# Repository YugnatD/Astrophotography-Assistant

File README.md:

# Astrophotography-Assistant

The project has two utility :
Make an automatic regulation of the temperature of the mirror of a newtonian telescope.
Recreate a card to controle motor of a NEQ5 mount, to add more correction speed, and planetary speed.

There is a raspberry pi integrated to the card that can control a guiding camera using PHD2.

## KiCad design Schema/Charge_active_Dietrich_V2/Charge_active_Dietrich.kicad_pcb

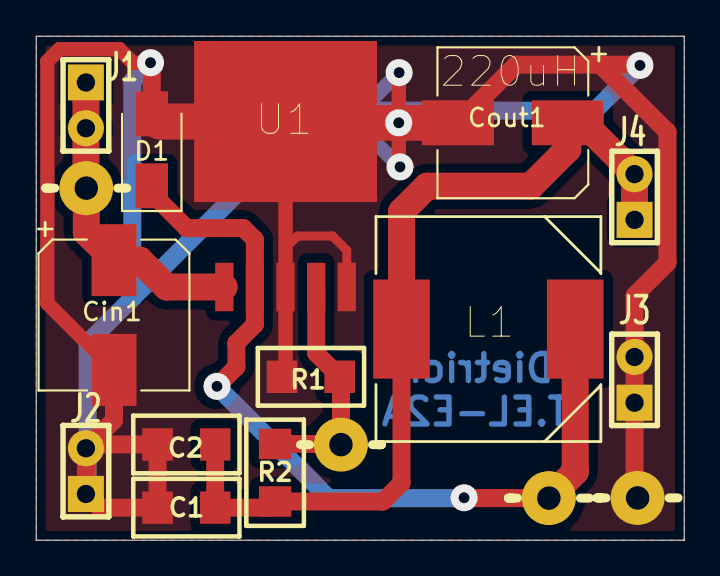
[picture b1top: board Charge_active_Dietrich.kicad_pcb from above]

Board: 2 copper layers, 36.0 x 28.0 mm, 17 parts (0 on the bottom side), 5 nets.

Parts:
C1, C2: C; SM_C_1206
Cin1: 100uF; CP_Elec_8x10
Cout1: 100uF; CP_Elec_8x10
D1: MBR340; D_SMA
J1, J2, J3, J4: CON2; TSC_CON2_SIL
J5, J6, J7, J8: CON1; TSC_CON1_poignard
L1: 220uH; INDM125125X800N
R1: 1K; SM_R_1206
R2: 3K; SM_R_1206
U1: LM2575HVS-ADJ; TO170P1435X457-6N

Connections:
GND: C1.2, C2.2, Cin1.2, Cout1.2, D1.2, J2.1, J2.2, J3.1, J3.2, J5.1, R1.2, U1.3, U1.5, U1.6
unnamed: C1.1, C2.1, Cout1.1, J4.1, J4.2, L1.2, R2.1
unnamed: Cin1.1, J1.1, J1.2, J8.1, U1.1
unnamed: D1.1, J6.1, L1.1, U1.2
unnamed: J7.1, R1.1, R2.2, U1.4

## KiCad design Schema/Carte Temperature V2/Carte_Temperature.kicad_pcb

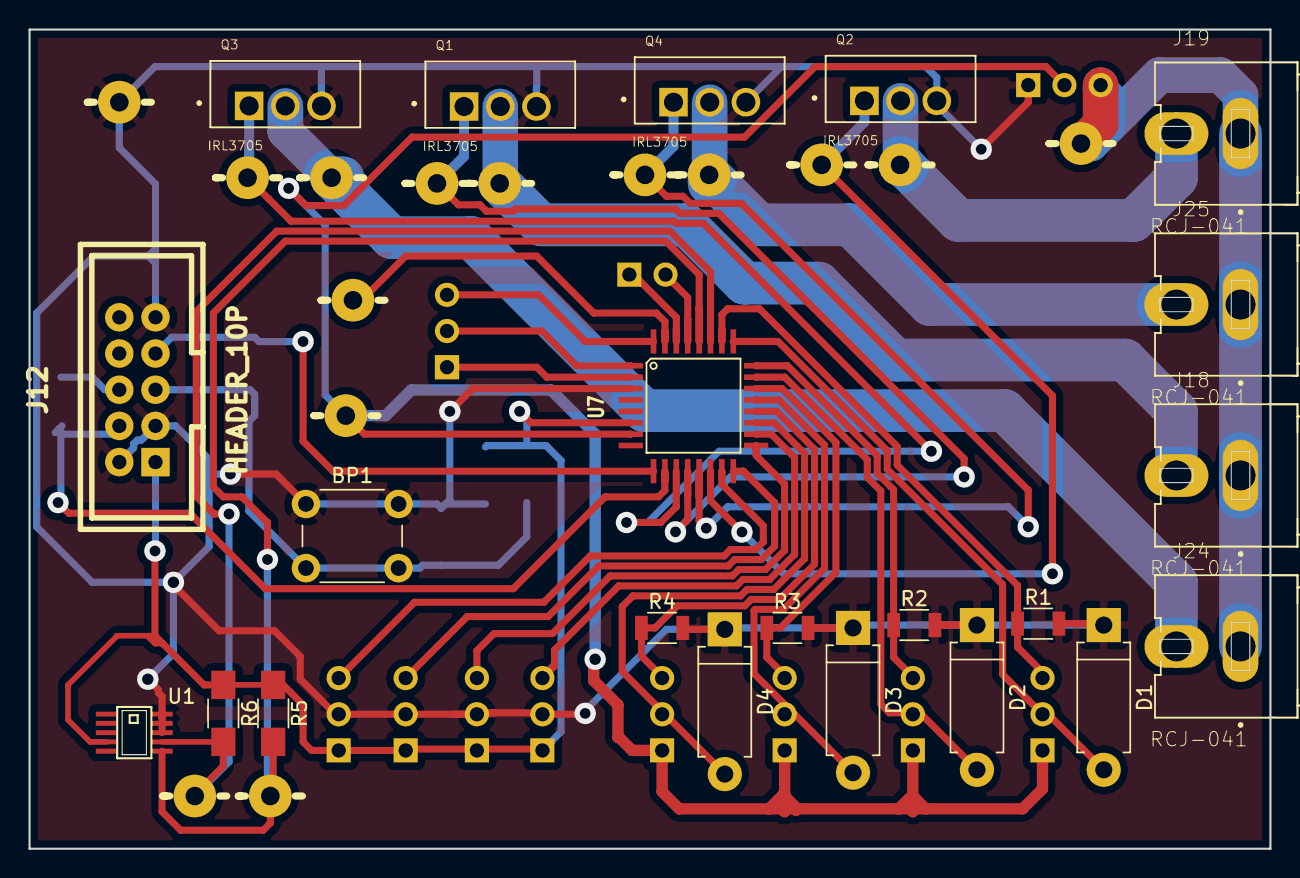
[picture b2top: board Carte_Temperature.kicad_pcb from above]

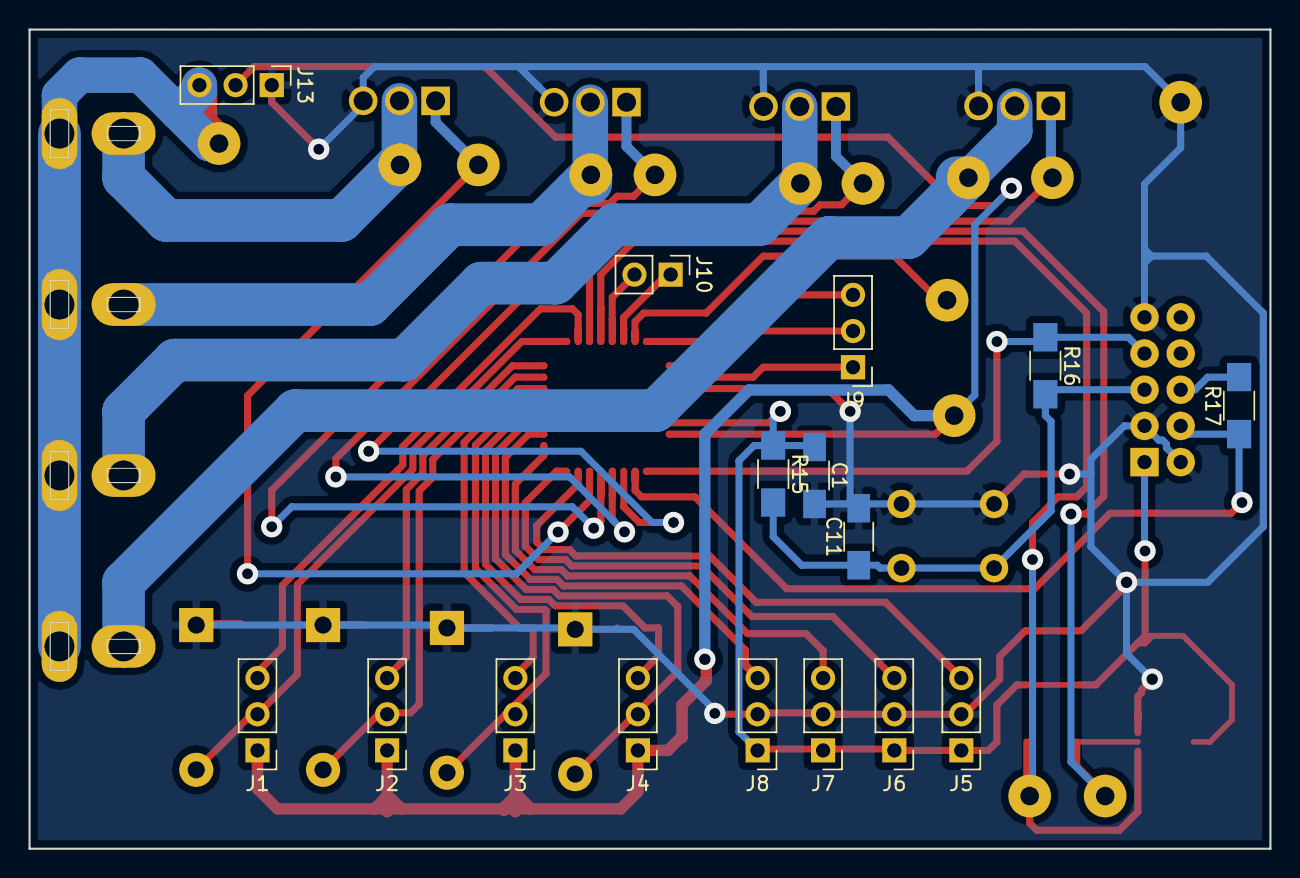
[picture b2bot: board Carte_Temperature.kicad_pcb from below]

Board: 2 copper layers, 87.1 x 57.5 mm, 52 parts (16 on the bottom side), 36 nets.

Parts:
BP1: POUSSOIR_ON; SW_PUSH_6mm
C1: C; C_1206_HandSoldering
C11: 1uF; C_1206_HandSoldering
D1, D2, D3, D4: D; D_DO-15_P10.16mm_Horizontal
J1, J2, J3, J4, J5, J6, J7, J8, J9, J13: Conn_01x03; Pin_Header_Straight_1x03_Pitch2.54mm
J10: Conn_01x02; Pin_Header_Straight_1x02_Pitch2.54mm
J11, J14, J15, J16, J17, J20, J21, J22, J23, J26, J27, J28, J29, J30: Conn_01x01; TSC_CON1_poignard
J12: HEADER_10P; JTAG
J18, J19, J24, J25: RCJ-041; CUI_RCJ-041_Graveuse
Q1, Q2, Q3, Q4: IRL3705; TO254P1052X465X1989-3-IRL3705
R1, R2, R3, R4: 18k; R_1206
R5, R6: R; R_1206_HandSoldering
R15, R16, R17: 1K; R_1206_HandSoldering
U1: EEH210; EEH210_1.5mm
U7: C8051F38C

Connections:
/C8051F38C/P0.0: J9.1, U7.2
/C8051F38C/P0.1: J9.2, U7.1
/C8051F38C/P0.2: J9.3, U7.32
/C8051F38C/P0.3: J11.1, U7.31
/C8051F38C/P0.4: J10.1, U7.30
/C8051F38C/P0.5: J10.2, U7.29
/C8051F38C/P0.6: J26.1, R5.2, U1.6, U7.28
/C8051F38C/P0.7: J27.1, R6.2, U1.7, U7.27
GND: BP1.1, C1.2, C11.2, D1.1, D2.1, D3.1, D4.1, J5.2, J6.2, J7.2, J8.2, J12.2, J12.3, J12.9, J13.1, J30.1, Q1.3, Q2.3, Q3.3, Q4.3, R1.2, R2.2, R3.2, R4.2, U1.8, U1.9, U1.10, U7.3
LM35_0_NEG: D1.2, J1.2, U7.25
LM35_0_POS: J1.3, R1.1, U7.26
LM35_1_NEG: D2.2, J2.2, U7.23
LM35_1_POS: J2.3, R2.1, U7.24
LM35_2_NEG: D3.2, J3.2, U7.21
LM35_2_POS: J3.3, R3.1, U7.22
LM35_3_NEG: D4.2, J4.2, U7.19
LM35_3_POS: J4.3, R4.1, U7.20
unnamed: BP1.2, C11.1, J12.5, R15.2, R16.2
unnamed: J12.4, R17.1, U7.10
unnamed: J12.6, R17.2
unnamed: J12.7, R16.1, U7.9
unnamed: J16.1, J18.2, Q1.2
unnamed: J17.1, J19.2, Q2.2
unnamed: J22.1, J24.2, Q3.2
unnamed: J23.1, J25.2, Q4.2
PCA0: J15.1, Q2.1, U7.14
PCA1: J21.1, Q4.1, U7.13
PCA2: J14.1, Q1.1, U7.12
PCA3: J20.1, Q3.1, U7.11
POT_0: J8.3, U7.18
POT_1: J7.3, U7.17
POT_2: J6.3, U7.16
POT_3: J5.3, U7.15
V(12V): J13.3, J18.1, J19.1, J24.1, J25.1, J29.1
VCC(5V): J1.1, J2.1, J3.1, J4.1, J13.2, J28.1, U7.7
VDD(3.3V): C1.1, J5.1, J6.1, J7.1, J8.1, J12.1, R5.1, R6.1, R15.1, U1.4, U7.6

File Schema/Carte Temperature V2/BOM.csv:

Source:;C:/Users/DIETRICHT_ELEC/Desktop/Diplome_Telescope_Dietrich_V17/Kicad_Telescope_V6/Carte Temperature V2/Carte_Temperature.sch;;;;;
Date:;24.05.2019 10:35;;;;;
Tool:;Eeschema 4.0.7;;;;;
Generator:;C:/Program Files/KiCad/bin/scripting/plugins/bom_csv_grouped_by_value.py;;;;;
Component Count:;52;;;;;
;;;;;;
Individual Components:;;;;;;
;;;;;;
Item;Qty;Reference(s);Value;LibPart;Footprint;Datasheet
;;BP1;POUSSOIR_ON;Carte_Temperature-cache:POUSSOIR_ON;Buttons_Switches_THT:SW_PUSH_6mm;
;;C1;100nF;device:C;Capacitors_SMD:C_1206_HandSoldering;
;;C11;1uF;device:C;Capacitors_SMD:C_1206_HandSoldering;
;;D1;D;device:D;Diodes_THT:D_DO-15_P10.16mm_Horizontal;
;;D2;D;device:D;Diodes_THT:D_DO-15_P10.16mm_Horizontal;
;;D3;D;device:D;Diodes_THT:D_DO-15_P10.16mm_Horizontal;
;;D4;D;device:D;Diodes_THT:D_DO-15_P10.16mm_Horizontal;
;;J1;Conn_01x03;conn:Conn_01x03;Pin_Headers:Pin_Header_Straight_1x03_Pitch2.54mm;
;;J2;Conn_01x03;conn:Conn_01x03;Pin_Headers:Pin_Header_Straight_1x03_Pitch2.54mm;
;;J3;Conn_01x03;conn:Conn_01x03;Pin_Headers:Pin_Header_Straight_1x03_Pitch2.54mm;
;;J4;Conn_01x03;conn:Conn_01x03;Pin_Headers:Pin_Header_Straight_1x03_Pitch2.54mm;
;;J5;Conn_01x03;conn:Conn_01x03;Pin_Headers:Pin_Header_Straight_1x03_Pitch2.54mm;
;;J6;Conn_01x03;conn:Conn_01x03;Pin_Headers:Pin_Header_Straight_1x03_Pitch2.54mm;
;;J7;Conn_01x03;conn:Conn_01x03;Pin_Headers:Pin_Header_Straight_1x03_Pitch2.54mm;
;;J8;Conn_01x03;conn:Conn_01x03;Pin_Headers:Pin_Header_Straight_1x03_Pitch2.54mm;
;;J9;Conn_01x03;conn:Conn_01x03;Pin_Headers:Pin_Header_Straight_1x03_Pitch2.54mm;
;;J10;Conn_01x02;conn:Conn_01x02;Pin_Headers:Pin_Header_Straight_1x02_Pitch2.54mm;
;;J11;Conn_01x01;conn:Conn_01x01;base_V2:TSC_CON1_poignard;
;;J12;HEADER_10P;Carte_Temperature-cache:HEADER_10P;Carte_Temperature:JTAG;
;;J13;Conn_01x03;conn:Conn_01x03;Pin_Headers:Pin_Header_Straight_1x03_Pitch2.54mm;
;;J14;Conn_01x01;conn:Conn_01x01;base_V2:TSC_CON1_poignard;
;;J15;Conn_01x01;conn:Conn_01x01;base_V2:TSC_CON1_poignard;
;;J16;Conn_01x01;conn:Conn_01x01;base_V2:TSC_CON1_poignard;
;;J17;Conn_01x01;conn:Conn_01x01;base_V2:TSC_CON1_poignard;
;;J18;RCJ-041;Carte_Temperature:RCJ-041;Carte_Temperature:CUI_RCJ-041_Graveuse;RCJ-041
;;J19;RCJ-041;Carte_Temperature:RCJ-041;Carte_Temperature:CUI_RCJ-041_Graveuse;RCJ-041
;;J20;Conn_01x01;conn:Conn_01x01;base_V2:TSC_CON1_poignard;
;;J21;Conn_01x01;conn:Conn_01x01;base_V2:TSC_CON1_poignard;
;;J22;Conn_01x01;conn:Conn_01x01;base_V2:TSC_CON1_poignard;
;;J23;Conn_01x01;conn:Conn_01x01;base_V2:TSC_CON1_poignard;
;;J24;RCJ-041;Carte_Temperature:RCJ-041;Carte_Temperature:CUI_RCJ-041_Graveuse;RCJ-041
;;J25;RCJ-041;Carte_Temperature:RCJ-041;Carte_Temperature:CUI_RCJ-041_Graveuse;RCJ-041
;;J26;Conn_01x01;conn:Conn_01x01;base_V2:TSC_CON1_poignard;
;;J27;Conn_01x01;conn:Conn_01x01;base_V2:TSC_CON1_poignard;
;;J28;Conn_01x01;conn:Conn_01x01;base_V2:TSC_CON1_poignard;
;;J29;Conn_01x01;conn:Conn_01x01;base_V2:TSC_CON1_poignard;
;;J30;Conn_01x01;conn:Conn_01x01;base_V2:TSC_CON1_poignard;
;;Q1;IRL3705;Carte_Temperature:IRL3705;Carte_Temperature:TO254P1052X465X1989-3-IRL3705;
;;Q2;IRL3705;Carte_Temperature:IRL3705;Carte_Temperature:TO254P1052X465X1989-3-IRL3705;
;;Q3;IRL3705;Carte_Temperature:IRL3705;Carte_Temperature:TO254P1052X465X1989-3-IRL3705;
;;Q4;IRL3705;Carte_Temperature:IRL3705;Carte_Temperature:TO254P1052X465X1989-3-IRL3705;
;;R1;18k;device:R;Resistors_SMD:R_1206_HandSoldering;
;;R2;18k;device:R;Resistors_SMD:R_1206_HandSoldering;
;;R3;18k;device:R;Resistors_SMD:R_1206_HandSoldering;
;;R4;18k;device:R;Resistors_SMD:R_1206_HandSoldering;
;;R5;1k;device:R;Resistors_SMD:R_1206_HandSoldering;
;;R6;1k;device:R;Resistors_SMD:R_1206_HandSoldering;
;;R15;1K;device:R;Resistors_SMD:R_1206_HandSoldering;
;;R16;1K;device:R;Resistors_SMD:R_1206_HandSoldering;
;;R17;1K;device:R;Resistors_SMD:R_1206_HandSoldering;
;;U1;EEH210;Carte_Temperature:EEH210;Carte_Temperature:EEH210_1.5mm;
;;U7;C8051F38C;Carte_Temperature-cache:C8051F38C;Carte_Temperature:C8051F38C;
;;;;;;
;;;;;;
;;;;;;
Collated Components:;;;;;;
;;;;;;
Item;Qty;Reference(s);Value;LibPart;Footprint;Datasheet
1;1;BP1;POUSSOIR_ON;Carte_Temperature-cache:POUSSOIR_ON;Buttons_Switches_THT:SW_PUSH_6mm;
2;1;C1;100nF;device:C;Capacitors_SMD:C_1206_HandSoldering;
3;1;C11;1uF;device:C;Capacitors_SMD:C_1206_HandSoldering;
4;4;"D1; D2; D3; D4";D;device:D;Diodes_THT:D_DO-15_P10.16mm_Horizontal;
5;10;"J1; J2; J3; J4; J5; J6; J7; J8; J9; J13";Conn_01x03;conn:Conn_01x03;Pin_Headers:Pin_Header_Straight_1x03_Pitch2.54mm;
6;1;J10;Conn_01x02;conn:Conn_01x02;Pin_Headers:Pin_Header_Straight_1x02_Pitch2.54mm;
7;14;"J11; J14; J15; J16; J17; J20; J21; J22; J23; J26; J27; J28; J29; J30";Conn_01x01;conn:Conn_01x01;base_V2:TSC_CON1_poignard;
8;1;J12;HEADER_10P;Carte_Temperature-cache:HEADER_10P;Carte_Temperature:JTAG;
9;4;"J18; J19; J24; J25";RCJ-041;Carte_Temperature:RCJ-041;Carte_Temperature:CUI_RCJ-041_Graveuse;RCJ-041
10;4;"Q1; Q2; Q3; Q4";IRL3705;Carte_Temperature:IRL3705;Carte_Temperature:TO254P1052X465X1989-3-IRL3705;
11;4;"R1; R2; R3; R4";18k;device:R;Resistors_SMD:R_1206_HandSoldering;
12;2;"R5; R6";1k;device:R;Resistors_SMD:R_1206_HandSoldering;
13;3;"R15; R16; R17";1K;device:R;Resistors_SMD:R_1206_HandSoldering;
14;1;U1;EEH210;Carte_Temperature:EEH210;Carte_Temperature:EEH210_1.5mm;
15;1;U7;C8051F38C;Carte_Temperature-cache:C8051F38C;Carte_Temperature:C8051F38C;

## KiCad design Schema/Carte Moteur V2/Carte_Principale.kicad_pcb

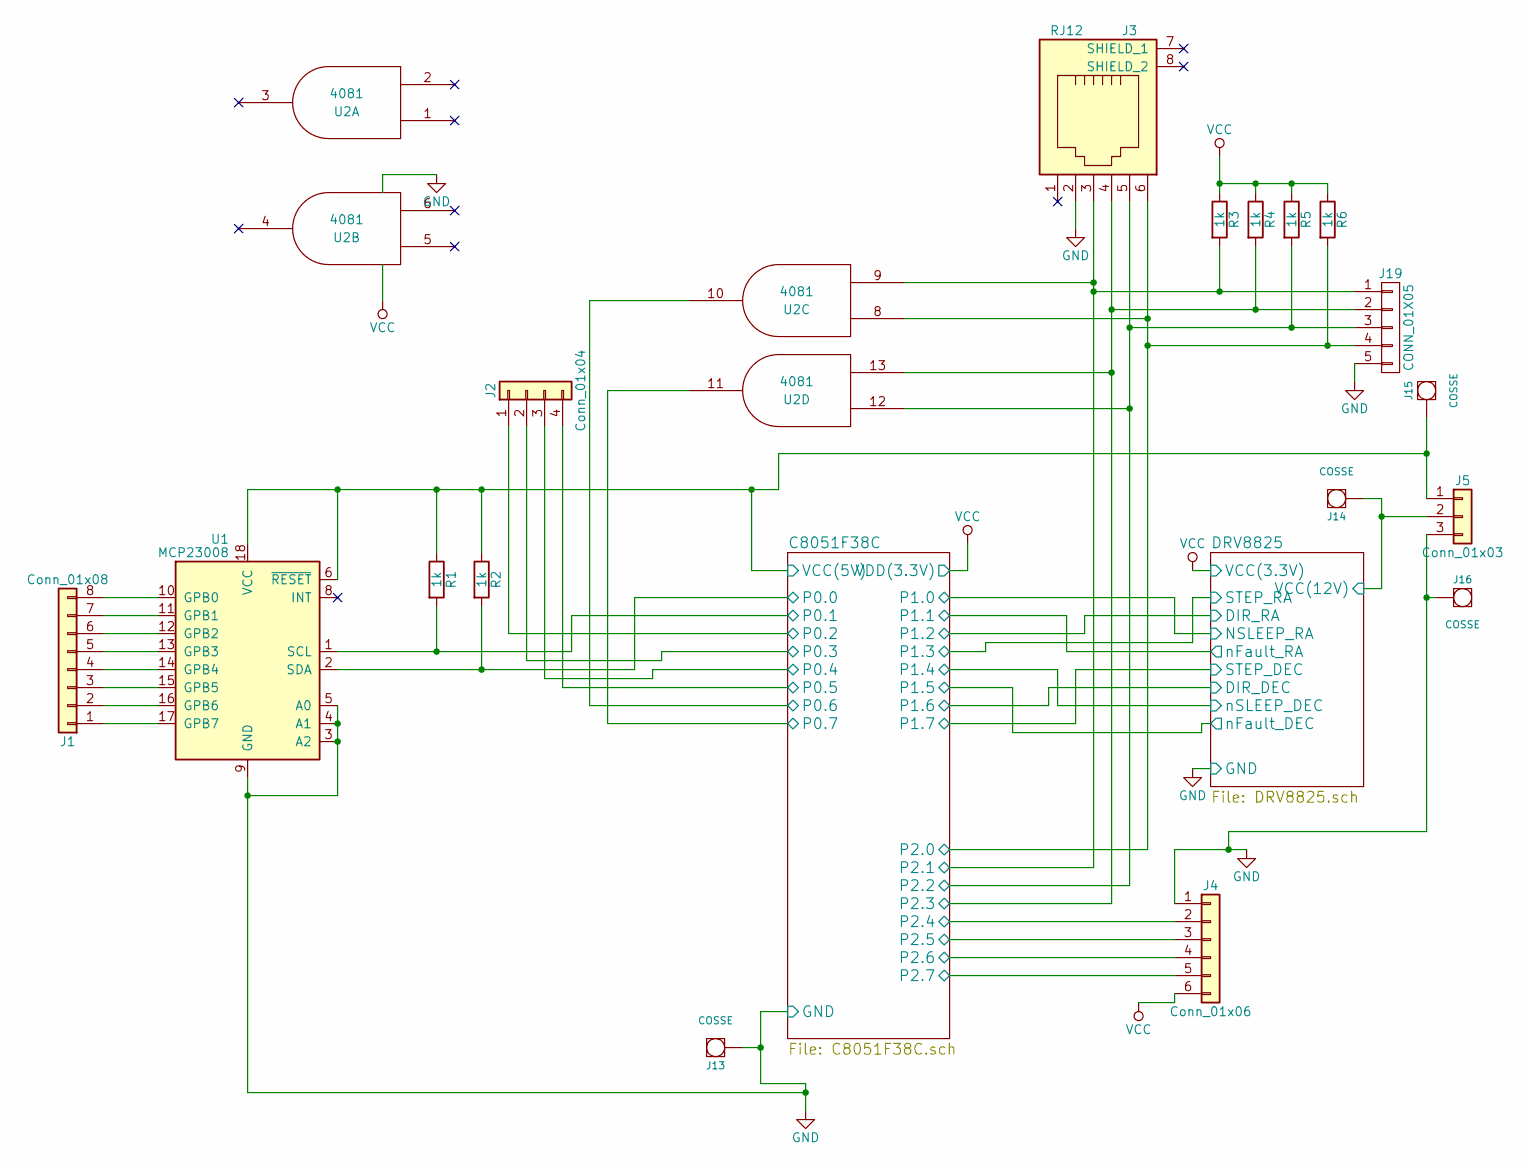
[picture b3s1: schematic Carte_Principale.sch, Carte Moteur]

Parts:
J1: Conn_01x08; Pin_Header_Straight_1x08
J2: Conn_01x04; Pin_Header_Straight_1x04
J3: RJ12
J4: Conn_01x06; Pin_Header_Straight_1x06
J5: Conn_01x03; Pin_Header_Straight_1x03
J13, J14, J15, J16: COSSE; TSC_CON1_poignard
J19: CONN_01X05; Pin_Header_Straight_1x05_Pitch2.54mm
R1, R2, R3, R4, R5, R6: 1k; R_1206_HandSoldering
U1: MCP23008; SOIC-18
U2: 4081; SM_SO-14

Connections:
/C8051F38C/P0.0: R2.2, U1.2 (SDA); also elsewhere on the board
/C8051F38C/P0.1: R1.2, U1.1 (SCL); also elsewhere on the board
/C8051F38C/P0.2: J2.1; also elsewhere on the board
/C8051F38C/P0.3: J2.2; also elsewhere on the board
/C8051F38C/P0.4: J2.3; also elsewhere on the board
/C8051F38C/P0.5: J2.4; also elsewhere on the board
/C8051F38C/P0.6: U2.10; also elsewhere on the board
/C8051F38C/P0.7: U2.11; also elsewhere on the board
/C8051F38C/P2.0: J3.6, J19.4, R6.2, U2.8; also elsewhere on the board
/C8051F38C/P2.1: J3.3, J19.1, R3.2, U2.9; also elsewhere on the board
/C8051F38C/P2.2: J3.5, J19.3, R5.2, U2.12; also elsewhere on the board
/C8051F38C/P2.3: J3.4, J19.2, R4.2, U2.13; also elsewhere on the board
/C8051F38C/P2.4: J4.2; also elsewhere on the board
/C8051F38C/P2.5: J4.3; also elsewhere on the board
/C8051F38C/P2.6: J4.4; also elsewhere on the board
/C8051F38C/P2.7: J4.5; also elsewhere on the board
/C8051F38C/VCC(5V): J5.1, J15.1, R1.1, R2.1, U1.6 (~RESET), U1.18 (VCC); also elsewhere on the board
/DRV8825/VCC(12V): J5.2, J14.1; also elsewhere on the board
GND: J3.2, J4.1, J5.3, J13.1, J16.1, J19.5, U1.3 (A2), U1.4 (A1), U1.5 (A0), U1.9 (GND), U2.7 (VSS); also elsewhere on the board
unnamed: J1.1, U1.17 (GPB7)
unnamed: J1.2, U1.16 (GPB6)
unnamed: J1.3, U1.15 (GPB5)
unnamed: J1.4, U1.14 (GPB4)
unnamed: J1.5, U1.13 (GPB3)
unnamed: J1.6, U1.12 (GPB2)
unnamed: J1.7, U1.11 (GPB1)
unnamed: J1.8, U1.10 (GPB0)
VCC: J4.6, R3.1, R4.1, R5.1, R6.1, U2.14 (VDD); also elsewhere on the board

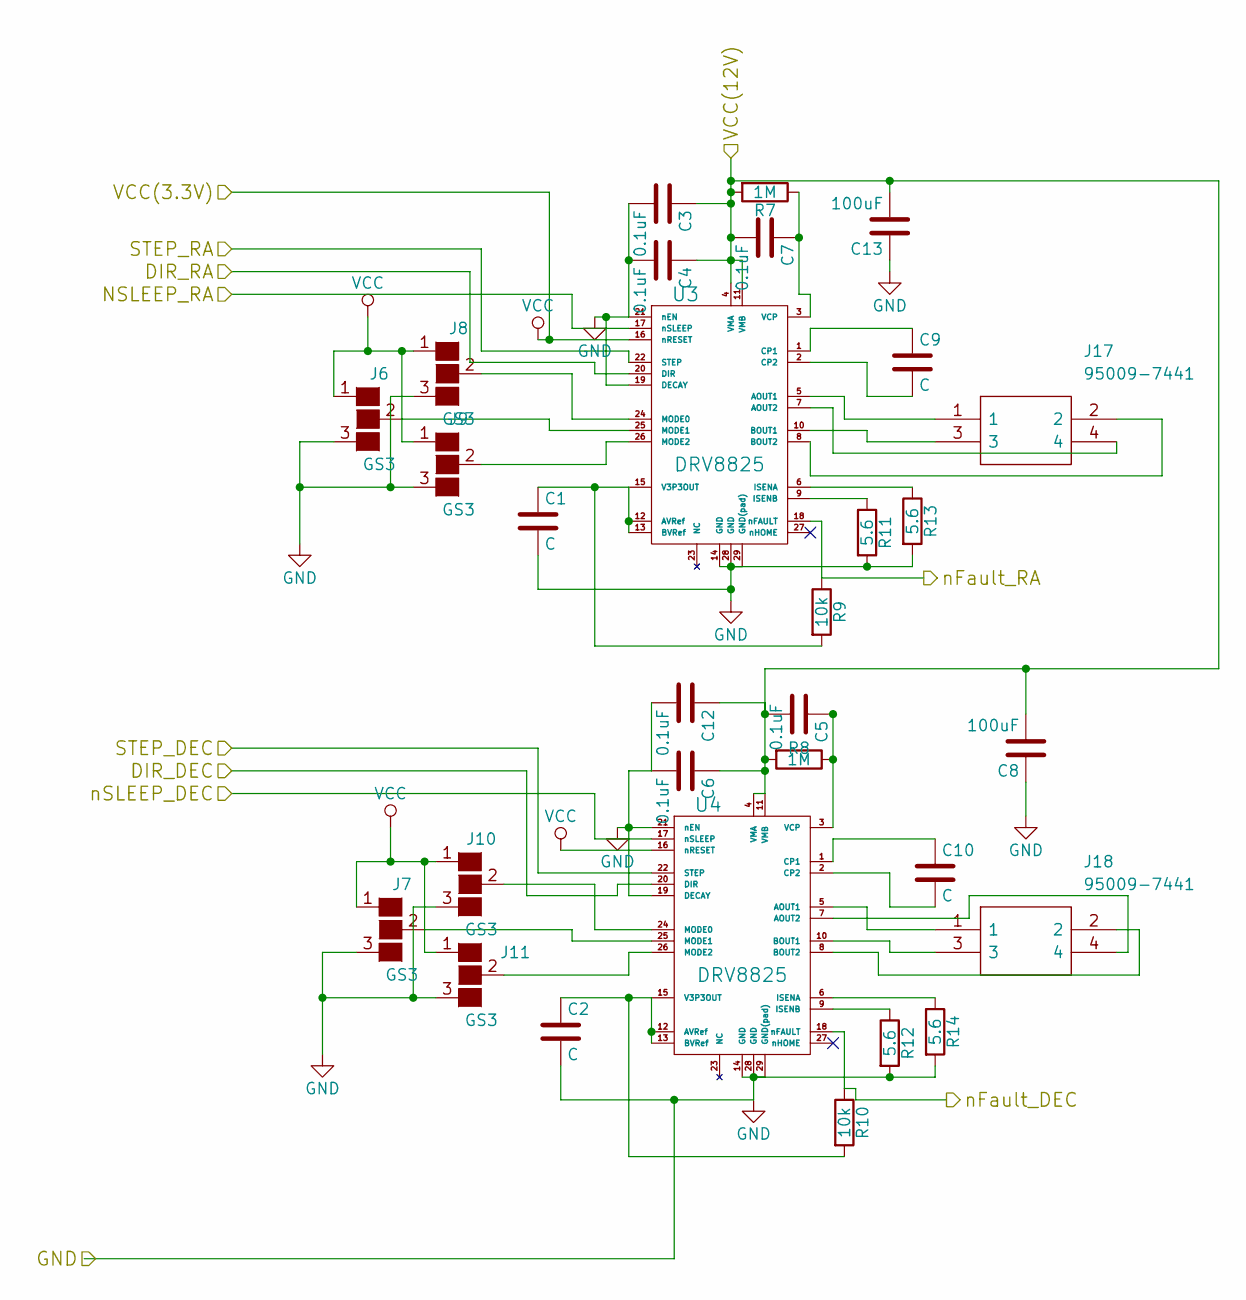
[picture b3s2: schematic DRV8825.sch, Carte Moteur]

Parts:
C1, C2, C9, C10: C; C_1206_HandSoldering
C3, C4, C5, C6, C7, C12: 0.1uF; C_1206_HandSoldering
C8, C13: 100uF; CP_Radial_D5.0mm_P2.00mm
J6, J7, J8, J9, J10, J11: GS3
J17, J18: 95009-7441; RJ11-95009-7441; Mouser Part Number 538-95009-7441
R7, R8: 1M; R_1206_HandSoldering
R9, R10: 10k; R_1206_HandSoldering
R11, R12, R13, R14: 5.6; R_1206_HandSoldering
U3, U4: DRV8825

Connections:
/C8051F38C/P1.1: R9.1, U3.18 (nFAULT); also elsewhere on the board
/C8051F38C/P1.3: U3.22 (STEP); also elsewhere on the board
/C8051F38C/P1.4: U4.17 (nSLEEP); also elsewhere on the board
/C8051F38C/P1.5: R10.1, U4.18 (nFAULT); also elsewhere on the board
/C8051F38C/P1.7: U4.22 (STEP); also elsewhere on the board
/DRV8825/DIR_DEC: U4.20 (DIR); also elsewhere on the board
/DRV8825/DIR_RA: U3.20 (DIR); also elsewhere on the board
/DRV8825/NSLEEP_RA: U3.17 (nSLEEP); also elsewhere on the board
/DRV8825/VCC(12V): C3.1, C4.1, C5.2, C6.1, C7.2, C8.2, C12.1, C13.2, R7.2, R8.2, U3.4 (VMA), U3.11 (VMB), U4.4 (VMA), U4.11 (VMB); also elsewhere on the board
GND: C1.2, C2.2, C3.2, C4.2, C6.2, C8.1, C12.2, C13.1, J6.3 (G3), J7.3 (G3), J8.3 (G3), J9.3 (G3), J10.3 (G3), J11.3 (G3), R11.2, R12.2, R13.2, R14.2, U3.14 (GND), U3.19 (DECAY), U3.21 (nEN), U3.28 (GND), U3.29 (GND(pad)), U4.14 (GND), U4.19 (DECAY), U4.21 (nEN), U4.28 (GND), U4.29 (GND(pad)); also elsewhere on the board
unnamed: C1.1, R9.2, U3.12 (AVRef), U3.13 (BVRef), U3.15 (V3P3OUT)
unnamed: C2.1, R10.2, U4.12 (AVRef), U4.13 (BVRef), U4.15 (V3P3OUT)
unnamed: C5.1, R8.1, U4.3 (VCP)
unnamed: C7.1, R7.1, U3.3 (VCP)
unnamed: C9.1, U3.1 (CP1)
unnamed: C9.2, U3.2 (CP2)
unnamed: C10.1, U4.1 (CP1)
unnamed: C10.2, U4.2 (CP2)
unnamed: J6.2 (G2), U3.25 (MODE1)
unnamed: J7.2 (G2), U4.25 (MODE1)
unnamed: J8.2 (G2), U3.24 (MODE0)
unnamed: J9.2 (G2), U3.26 (MODE2)
unnamed: J10.2 (G2), U4.24 (MODE0)
unnamed: J11.2 (G2), U4.26 (MODE2)
unnamed: J17.1, U3.5 (AOUT1)
unnamed: J17.2, U3.8 (BOUT2)
unnamed: J17.3, U3.10 (BOUT1)
unnamed: J17.4, U3.7 (AOUT2)
unnamed: J18.1, U4.5 (AOUT1)
unnamed: J18.2, U4.8 (BOUT2)
unnamed: J18.3, U4.10 (BOUT1)
unnamed: J18.4, U4.7 (AOUT2)
unnamed: R11.1, U3.9 (ISENB)
unnamed: R12.1, U4.9 (ISENB)
unnamed: R13.1, U3.6 (ISENA)
unnamed: R14.1, U4.6 (ISENA)
VCC: J6.1 (G1), J7.1 (G1), J8.1 (G1), J9.1 (G1), J10.1 (G1), J11.1 (G1), U3.16 (nRESET), U4.16 (nRESET); also elsewhere on the board

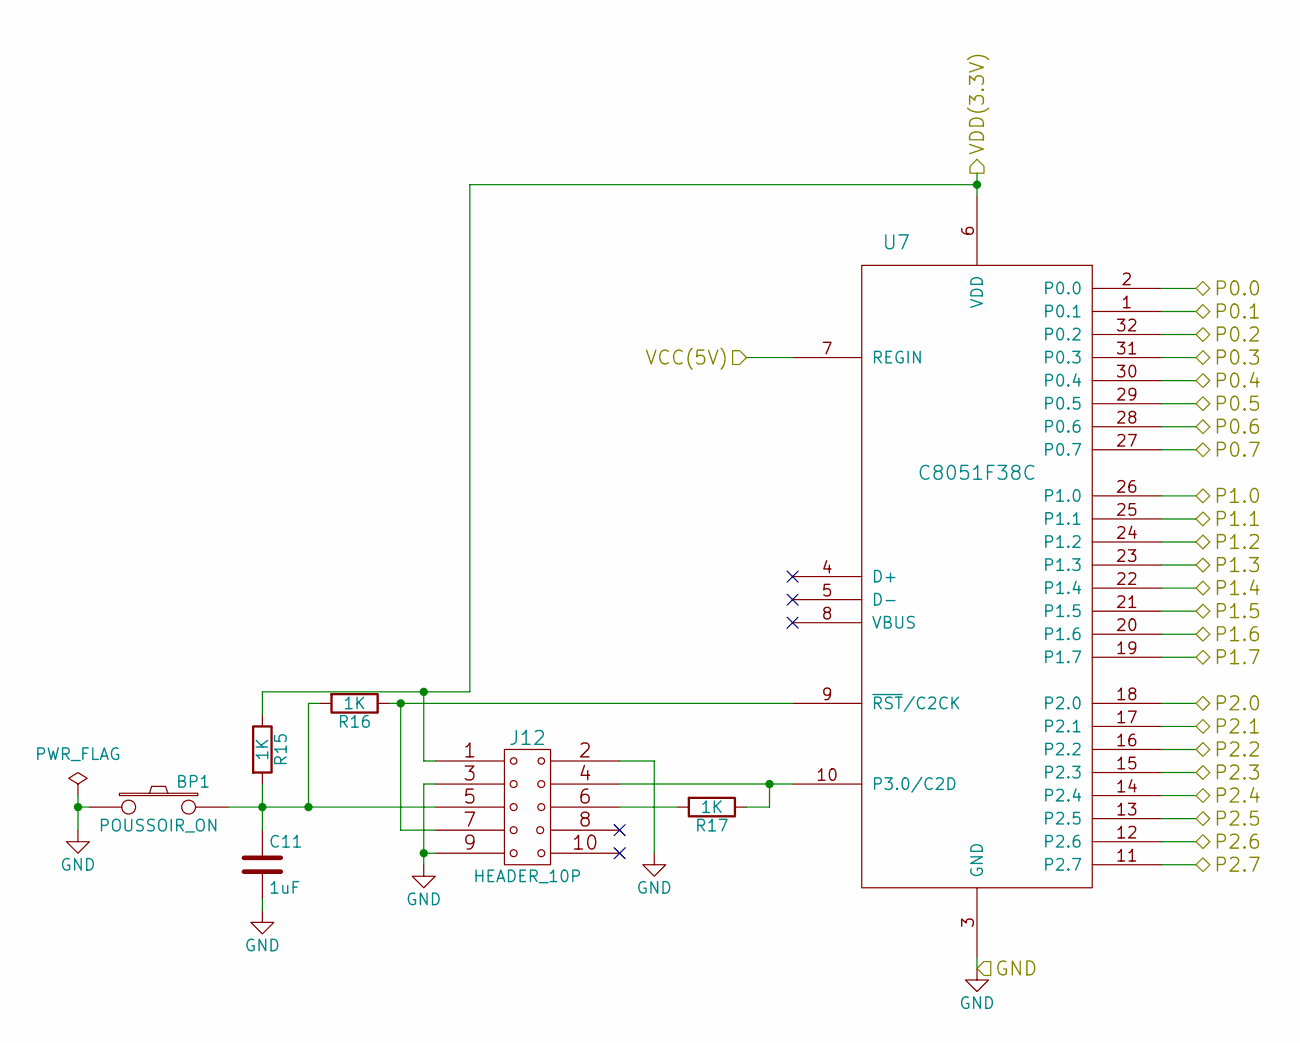
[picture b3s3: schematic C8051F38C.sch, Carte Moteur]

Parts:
BP1: POUSSOIR_ON; SW_PUSH_6mm
C11: 1uF; C_1206_HandSoldering
J12: HEADER_10P; JTAG
R15, R16, R17: 1K; R_1206_HandSoldering
U7: C8051F38C

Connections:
/C8051F38C/P0.0: U7.2 (P0.0); also elsewhere on the board
/C8051F38C/P0.1: U7.1 (P0.1); also elsewhere on the board
/C8051F38C/P0.2: U7.32 (P0.2); also elsewhere on the board
/C8051F38C/P0.3: U7.31 (P0.3); also elsewhere on the board
/C8051F38C/P0.4: U7.30 (P0.4); also elsewhere on the board
/C8051F38C/P0.5: U7.29 (P0.5); also elsewhere on the board
/C8051F38C/P0.6: U7.28 (P0.6); also elsewhere on the board
/C8051F38C/P0.7: U7.27 (P0.7); also elsewhere on the board
/C8051F38C/P1.1: U7.25 (P1.1); also elsewhere on the board
/C8051F38C/P1.3: U7.23 (P1.3); also elsewhere on the board
/C8051F38C/P1.4: U7.22 (P1.4); also elsewhere on the board
/C8051F38C/P1.5: U7.21 (P1.5); also elsewhere on the board
/C8051F38C/P1.7: U7.19 (P1.7); also elsewhere on the board
/C8051F38C/P2.0: U7.18 (P2.0); also elsewhere on the board
/C8051F38C/P2.1: U7.17 (P2.1); also elsewhere on the board
/C8051F38C/P2.2: U7.16 (P2.2); also elsewhere on the board
/C8051F38C/P2.3: U7.15 (P2.3); also elsewhere on the board
/C8051F38C/P2.4: U7.14 (P2.4); also elsewhere on the board
/C8051F38C/P2.5: U7.13 (P2.5); also elsewhere on the board
/C8051F38C/P2.6: U7.12 (P2.6); also elsewhere on the board
/C8051F38C/P2.7: U7.11 (P2.7); also elsewhere on the board
/C8051F38C/VCC(5V): U7.7 (REGIN); also elsewhere on the board
/DRV8825/DIR_DEC: U7.20 (P1.6); also elsewhere on the board
/DRV8825/DIR_RA: U7.24 (P1.2); also elsewhere on the board
/DRV8825/NSLEEP_RA: U7.26 (P1.0); also elsewhere on the board
GND: BP1.1, C11.2, J12.2, J12.3, J12.9, U7.3 (GND); also elsewhere on the board
unnamed: BP1.2, C11.1, J12.5, R15.2, R16.2
unnamed: J12.4, R17.1, U7.10 (P3.0/C2D)
unnamed: J12.6, R17.2
unnamed: J12.7, R16.1, U7.9 (~RST~/C2CK)
VCC: J12.1, R15.1, U7.6 (VDD); also elsewhere on the board

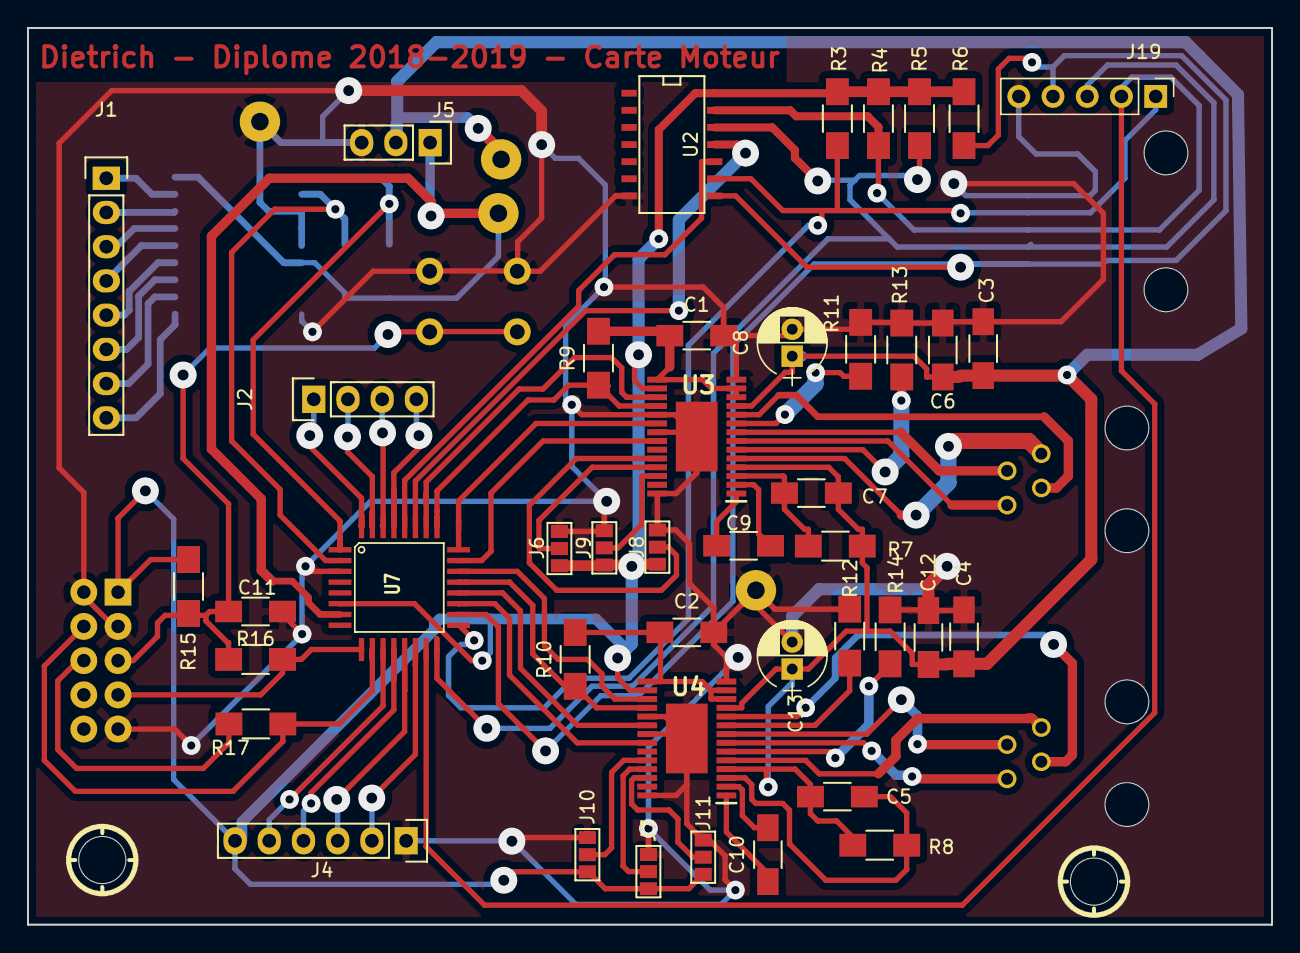
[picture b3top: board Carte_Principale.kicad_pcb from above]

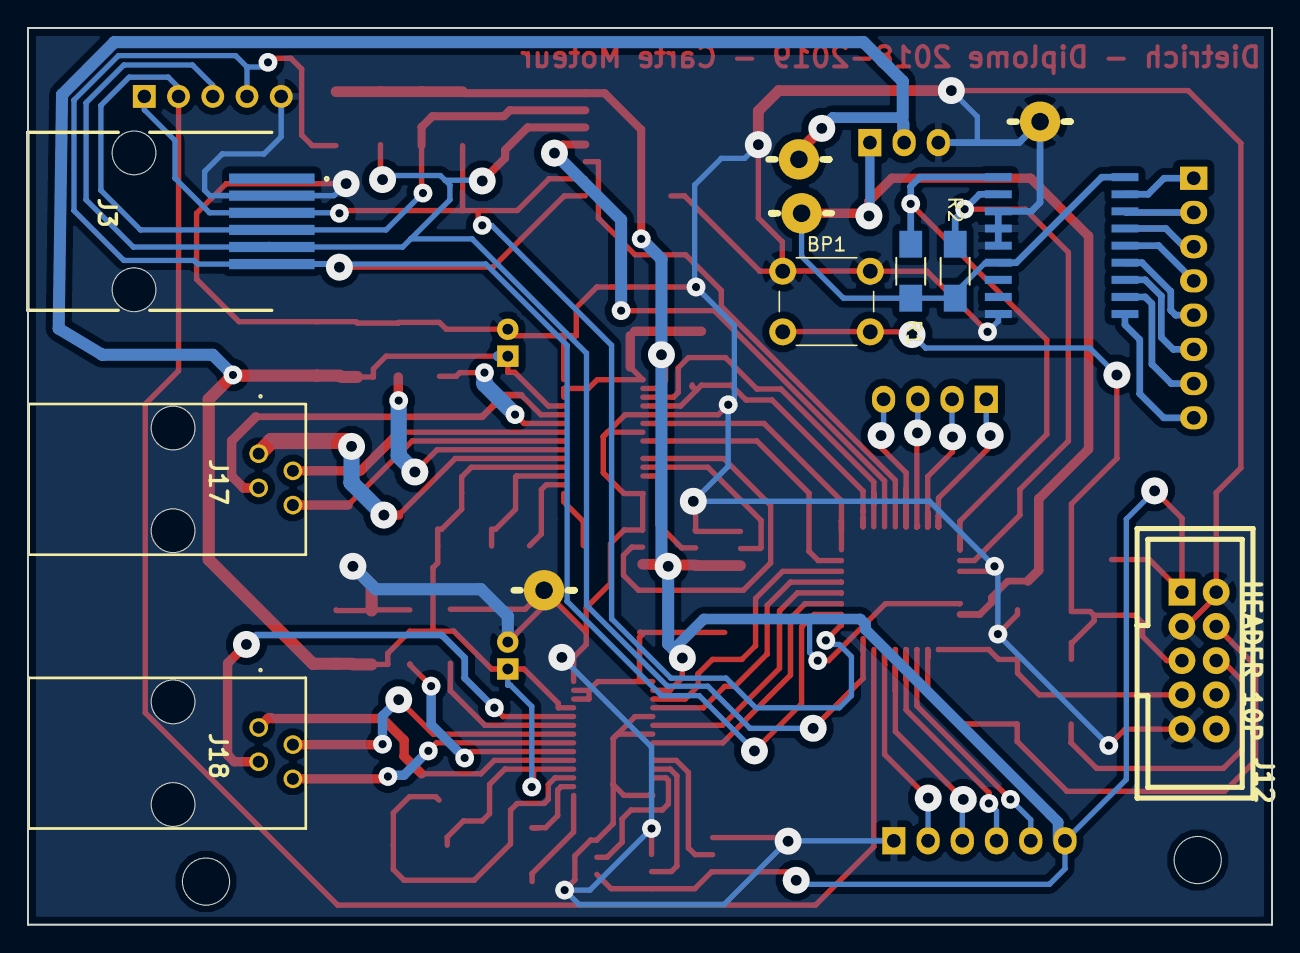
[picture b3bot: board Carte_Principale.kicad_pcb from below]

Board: 2 copper layers, 92.3 x 66.5 mm, 57 parts (12 on the bottom side), 66 nets.

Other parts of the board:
TROU_3.5, TROU_3.5#2: Val**; TROU_3.5

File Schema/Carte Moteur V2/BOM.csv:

Source:;;;;;;;;;;;
Date:;24.05.2019 10:07;;;;;;;;;;
Tool:;Eeschema 4.0.7;;;;;;;;;;
Generator:;;;;;;;;;;;
Component Count:;55;;;;;;;;;;
;;;;;;;;;;;
Individual Components:;;;;;;;;;;;
;;;;;;;;;;;
Item;Qty;Reference(s);Value;LibPart;Footprint;Datasheet;Description;Manufacturer_Name;Manufacturer_Part_Number;Mouser Part Number;Mouser Price/Stock
;;BP1;POUSSOIR_ON;Carte_Principale-cache:POUSSOIR_ON;Buttons_Switches_THT:SW_PUSH_6mm;;;;;;
;;C1;0.47uF;device:C;Capacitors_SMD:C_1206_HandSoldering;;;;;;
;;C2;0.47uF;device:C;Capacitors_SMD:C_1206_HandSoldering;;;;;;
;;C3;0.1uF;device:C;Capacitors_SMD:C_1206_HandSoldering;;;;;;
;;C4;0.1uF;device:C;Capacitors_SMD:C_1206_HandSoldering;;;;;;
;;C5;0.1uF;device:C;Capacitors_SMD:C_1206_HandSoldering;;;;;;
;;C6;0.1uF;device:C;Capacitors_SMD:C_1206_HandSoldering;;;;;;
;;C7;0.1uF;device:C;Capacitors_SMD:C_1206_HandSoldering;;;;;;
;;C8;100uF;device:C;Carte_Principale:CP_Radial_D5.0mm_P2.00mm;;;;;;
;;C9;0.01uF;device:C;Capacitors_SMD:C_1206_HandSoldering;;;;;;
;;C10;0.01uF;device:C;Capacitors_SMD:C_1206_HandSoldering;;;;;;
;;C11;1uF;device:C;Capacitors_SMD:C_1206_HandSoldering;;;;;;
;;C12;0.1uF;device:C;Capacitors_SMD:C_1206_HandSoldering;;;;;;
;;C13;100uF;device:C;Carte_Principale:CP_Radial_D5.0mm_P2.00mm;;;;;;
;;J1;Conn_01x08;conn:Conn_01x08;Pin_Headers:Pin_Header_Straight_1x08;;;;;;
;;J2;Conn_01x04;conn:Conn_01x04;Pin_Headers:Pin_Header_Straight_1x04;;;;;;
;;J3;RJ12;conn:RJ12;Carte_Principale:RJ12;;;;;;
;;J4;Conn_01x06;conn:Conn_01x06;Pin_Headers:Pin_Header_Straight_1x06;;;;;;
;;J5;Conn_01x03;conn:Conn_01x03;Pin_Headers:Pin_Header_Straight_1x03;;;;;;
;;J6;GS3;conn:GS3;Connectors:GS3;;;;;;
;;J7;GS3;conn:GS3;Connectors:GS3;;;;;;
;;J8;GS3;conn:GS3;Connectors:GS3;;;;;;
;;J9;GS3;conn:GS3;Connectors:GS3;;;;;;
;;J10;GS3;conn:GS3;Connectors:GS3;;;;;;
;;J11;GS3;conn:GS3;Connectors:GS3;;;;;;
;;J12;HEADER_10P;Carte_Principale:HEADER_10P;Carte_Principale:JTAG;;;;;;
;;J13;COSSE;Carte_Principale-cache:COSSE;base_V2:TSC_CON1_poignard;;;;;;
;;J14;COSSE;Carte_Principale-cache:COSSE;base_V2:TSC_CON1_poignard;;;;;;
;;J15;COSSE;Carte_Principale-cache:COSSE;base_V2:TSC_CON1_poignard;;;;;;
;;J16;COSSE;Carte_Principale-cache:COSSE;base_V2:TSC_CON1_poignard;;;;;;
;;J17;95009-7441;Carte_Principale-cache:95009-7441;Carte_Principale:RJ11-95009-7441;https://componentsearchengine.com/Datasheets/1/95009-7441.pdf;"RJ11 R/A PCB modular jack; w/panel stops Molex 4P4C Right Angle PCB Mount RJ11 Modular Jack Connector 95009";Molex;95009-7441;538-95009-7441;https://www.mouser.com/Search/Refine.aspx?Keyword=538-95009-7441
;;J18;95009-7441;Carte_Principale-cache:95009-7441;Carte_Principale:RJ11-95009-7441;https://componentsearchengine.com/Datasheets/1/95009-7441.pdf;"RJ11 R/A PCB modular jack; w/panel stops Molex 4P4C Right Angle PCB Mount RJ11 Modular Jack Connector 95009";Molex;95009-7441;538-95009-7441;https://www.mouser.com/Search/Refine.aspx?Keyword=538-95009-7441
;;J19;CONN_01X05;Carte_Principale-cache:CONN_01X05;Pin_Headers:Pin_Header_Straight_1x05_Pitch2.54mm;;;;;;
;;R1;10k;device:R;Resistors_SMD:R_1206_HandSoldering;;;;;;
;;R2;10k;device:R;Resistors_SMD:R_1206_HandSoldering;;;;;;
;;R3;1k;device:R;Resistors_SMD:R_1206_HandSoldering;;;;;;
;;R4;1k;device:R;Resistors_SMD:R_1206_HandSoldering;;;;;;
;;R5;1k;device:R;Resistors_SMD:R_1206_HandSoldering;;;;;;
;;R6;1k;device:R;Resistors_SMD:R_1206_HandSoldering;;;;;;
;;R7;1M;device:R;Resistors_SMD:R_1206_HandSoldering;;;;;;
;;R8;1M;device:R;Resistors_SMD:R_1206_HandSoldering;;;;;;
;;R9;10k;device:R;Resistors_SMD:R_1206_HandSoldering;;;;;;
;;R10;10k;device:R;Resistors_SMD:R_1206_HandSoldering;;;;;;
;;R11;02.févr;device:R;Resistors_SMD:R_1206_HandSoldering;;;;;;
;;R12;02.févr;device:R;Resistors_SMD:R_1206_HandSoldering;;;;;;
;;R13;02.févr;device:R;Resistors_SMD:R_1206_HandSoldering;;;;;;
;;R14;02.févr;device:R;Resistors_SMD:R_1206_HandSoldering;;;;;;
;;R15;1K;device:R;Resistors_SMD:R_1206_HandSoldering;;;;;;
;;R16;1K;device:R;Resistors_SMD:R_1206_HandSoldering;;;;;;
;;R17;1K;device:R;Resistors_SMD:R_1206_HandSoldering;;;;;;
;;U1;MCP23008;microchip:MCP23008;Carte_Principale:SOIC-18;;;;;;
;;U2;4081;cmos4000:4081;base_V2:SM_SO-14;;;;;;
;;U3;DRV8825;Carte_Principale:DRV8825;Carte_Principale:DRV8825;;;;;;
;;U4;DRV8825;Carte_Principale:DRV8825;Carte_Principale:DRV8825;;;;;;
;;U7;C8051F38C;Carte_Principale:C8051F38C;Carte_Principale:C8051F38C;;;;;;
;;;;;;;;;;;
;;;;;;;;;;;
;;;;;;;;;;;
Collated Components:;;;;;;;;;;;
;;;;;;;;;;;
Item;Qty;Reference(s);Value;Empreinte;Footprint;Datasheet;Description;Manufacturer_Name;Manufacturer_Part_Number;Mouser Part Number;Mouser Price/Stock
1;1;BP1;POUSSOIR_ON;Buttons_Switches_THT:SW_PUSH_6mm;Buttons_Switches_THT:SW_PUSH_6mm;;;;;;
2;2;"C1; C2";0.47uF;SMD 1206;Capacitors_SMD:C_1206_HandSoldering;;;;;;
3;6;"C3; C4; C5; C6; C7; C12";0.1uF;SMD 1207;Capacitors_SMD:C_1206_HandSoldering;;;;;;
4;2;"C8; C13";100uF;SMD 1208;Carte_Principale:CP_Radial_D5.0mm_P2.00mm;;;;;;
5;2;"C9; C10";0.01uF;SMD 1209;Capacitors_SMD:C_1206_HandSoldering;;;;;;
6;1;C11;1uF;SMD 1210;Capacitors_SMD:C_1206_HandSoldering;;;;;;
7;1;J1;Conn_01x08;conn:Conn_01x08;Pin_Headers:Pin_Header_Straight_1x08;;;;;;
8;1;J2;Conn_01x04;conn:Conn_01x04;Pin_Headers:Pin_Header_Straight_1x04;;;;;;
9;1;J3;RJ12;conn:RJ12;Carte_Principale:RJ12;;;;;;
10;1;J4;Conn_01x06;conn:Conn_01x06;Pin_Headers:Pin_Header_Straight_1x06;;;;;;
11;1;J5;Conn_01x03;conn:Conn_01x03;Pin_Headers:Pin_Header_Straight_1x03;;;;;;
;;;;;;;;;;;
;1;J12;HEADER_10P;Carte_Principale:HEADER_10P;Carte_Principale:JTAG;;;;;;
;4;"J13; J14; J15; J16";COSSE;Carte_Principale-cache:COSSE;base_V2:TSC_CON1_poignard;;;;;;
;2;"J17; J18";95009-7441;Carte_Principale-cache:95009-7441;Carte_Principale:RJ11-95009-7441;https://componentsearchengine.com/Datasheets/1/95009-7441.pdf;"RJ11 R/A PCB modular jack; w/panel stops Molex 4P4C Right Angle PCB Mount RJ11 Modular Jack Connector 95009";Molex;95009-7441;538-95009-7441;https://www.mouser.com/Search/Refine.aspx?Keyword=538-95009-7441
;1;J19;CONN_01X05;Carte_Principale-cache:CONN_01X05;Pin_Headers:Pin_Header_Straight_1x05_Pitch2.54mm;;;;;;
;4;"R1; R2; R9; R10";10k;device:R;Resistors_SMD:R_1206_HandSoldering;;;;;;
;4;"R3; R4; R5; R6";1k;device:R;Resistors_SMD:R_1206_HandSoldering;;;;;;
;2;"R7; R8";1M;device:R;Resistors_SMD:R_1206_HandSoldering;;;;;;
;4;"R11; R12; R13; R14";02.févr;device:R;Resistors_SMD:R_1206_HandSoldering;;;;;;
;3;"R15; R16; R17";1K;device:R;Resistors_SMD:R_1206_HandSoldering;;;;;;
;1;U1;MCP23008;microchip:MCP23008;Carte_Principale:SOIC-18;;;;;;
;1;U2;4081;cmos4000:4081;base_V2:SM_SO-14;;;;;;
;2;"U3; U4";DRV8825;Carte_Principale:DRV8825;Carte_Principale:DRV8825;;;;;;
;1;U7;C8051F38C;Carte_Principale:C8051F38C;Carte_Principale:C8051F38C;;;;;;
